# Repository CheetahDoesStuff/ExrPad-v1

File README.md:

# ExrPad v1
The ExrPad v1 is a pretty small and neat macropad!

## Some words
Before i start, i just wanna thank @shadow and @rekirxs (both in the hackclub slack) for all the help through the process from the schematic to the case, couldnt have done it without you guys !

TODO: write smth here (i really wanna write this now but its 12 am and i need my 3 hours of netflix before i go to sleep)
## Details
### Specifications
The features include:
* A powerful microcontroller as the main piece in the device (Seed Studio XIAO rp2040)
* 6 Cherry MX switches that are fully programmable
* A rotary encoder and switch (pressable rotary encoder)
* A 128x32 OLED display

The entire thing is inside a neat package consiting a 3D printed case (top and bottom part)

## Repository
Folder structure:
```sh
ExrPad-v1 # Root
  /PCB # Folder containing all files for the PCB design
    ExrPad.kicad_pro # The main project file of the kiCAD project
    ExrPad.kicad_sch # KiCAD schematic
    ExrPad.kicad_pcb # KiCAD PCB Design
  /CAD # All files for the 3D design of the device
    ExrPad_v1_top_rev2.step # Top part of the case
    ExrPad_v1_bottom.step # Bottom part of the case
    ExrPad_v1_assembled.step # Full case with pcb and components, used for images
  /Firmware # All files related to the firmware/software side of the project
    TODO: This as well
```

## Images!
| Schematic       | PCB             | Case parts      | Full design (PCB and case) |
|-----------------|-----------------|-----------------|----------------------------|
|  |  |  |  |

## BOM
- Seeed XIAO RP2040 — x1
- MX-style mechanical switches — x6
- EC11 rotary encoder (with switch) — x1
- Blank DSA keycaps — x6
- 0.91 inch OLED display — x1
- M3 x 16 mm screws & M3 heat-set inserts — x4

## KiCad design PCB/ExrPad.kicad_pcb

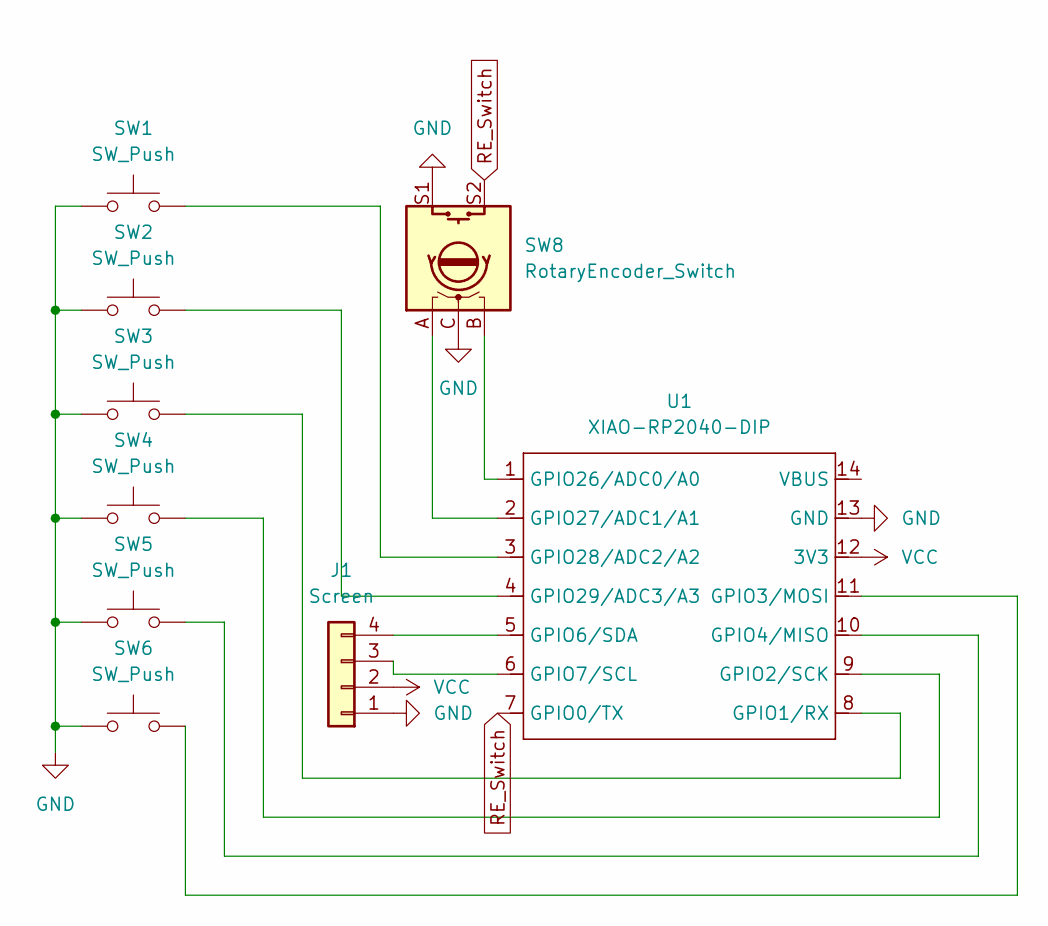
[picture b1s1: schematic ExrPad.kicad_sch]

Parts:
J1: Screen; PinHeader_1x04_P2.54mm_Vertical
SW1, SW2, SW3, SW4, SW5, SW6: SW_Push; SW_Cherry_MX_1.00u_PCB
SW8: RotaryEncoder_Switch; RotaryEncoder_Alps_EC11E-Switch_Vertical_H20mm
U1: XIAO-RP2040-DIP

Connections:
GND: J1.1, SW1.1, SW2.1, SW3.1, SW4.1, SW5.1, SW6.1, SW8.C, SW8.S1, U1.13 (GND)
unnamed: J1.3, U1.6 (GPIO7/SCL)
unnamed: J1.4, U1.5 (GPIO6/SDA)
unnamed: SW3.2, U1.8 (GPIO1/RX)
unnamed: SW4.2, U1.9 (GPIO2/SCK)
unnamed: SW6.2, U1.11 (GPIO3/MOSI)
unnamed: SW5.2, U1.10 (GPIO4/MISO)
unnamed: SW8.B, U1.1 (GPIO26/ADC0/A0)
unnamed: SW8.A, U1.2 (GPIO27/ADC1/A1)
unnamed: SW1.2, U1.3 (GPIO28/ADC2/A2)
unnamed: SW2.2, U1.4 (GPIO29/ADC3/A3)
RE_Switch: SW8.S2, U1.7 (GPIO0/TX)
VCC: J1.2, U1.12 (3V3)

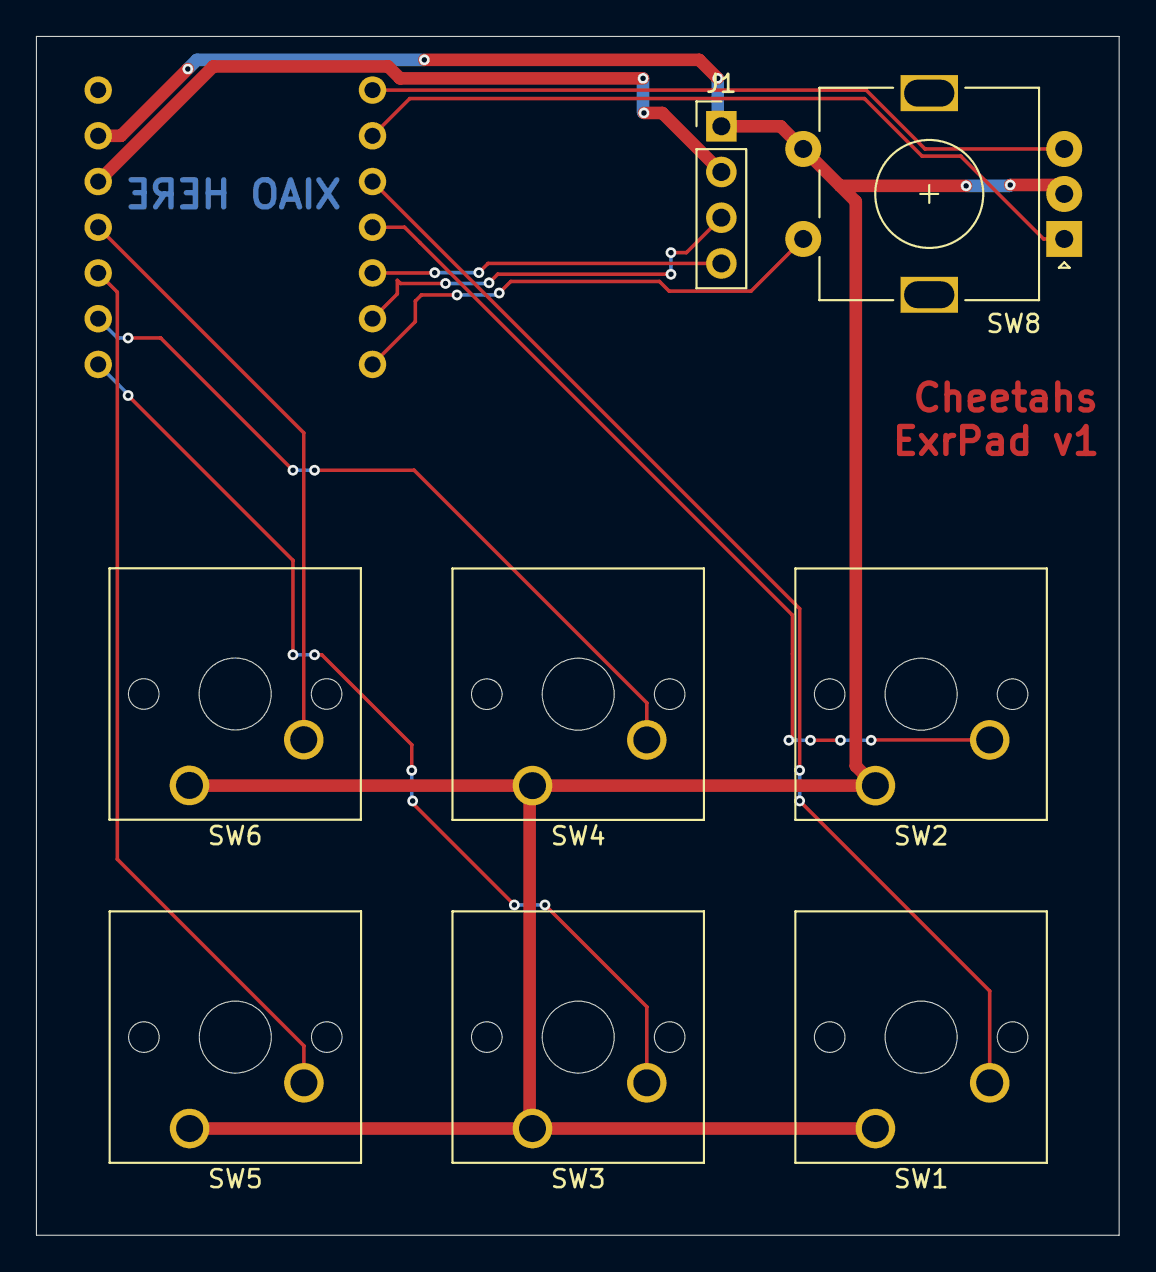
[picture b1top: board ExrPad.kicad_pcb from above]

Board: 2 copper layers, 60.2 x 66.6 mm, 9 parts (1 on the bottom side), 13 nets.

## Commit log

2026-01-01 Added pcb files
2026-01-01 Update README with project details and specifications
    Added detailed specifications and repository structure.
2026-01-02 Add BOM section to README
    Added Bill of Materials (BOM) section to README.
2026-01-02 Update top case file name in README
